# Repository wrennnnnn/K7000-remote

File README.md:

# K7000-remote
An OSH k7000 remote board.

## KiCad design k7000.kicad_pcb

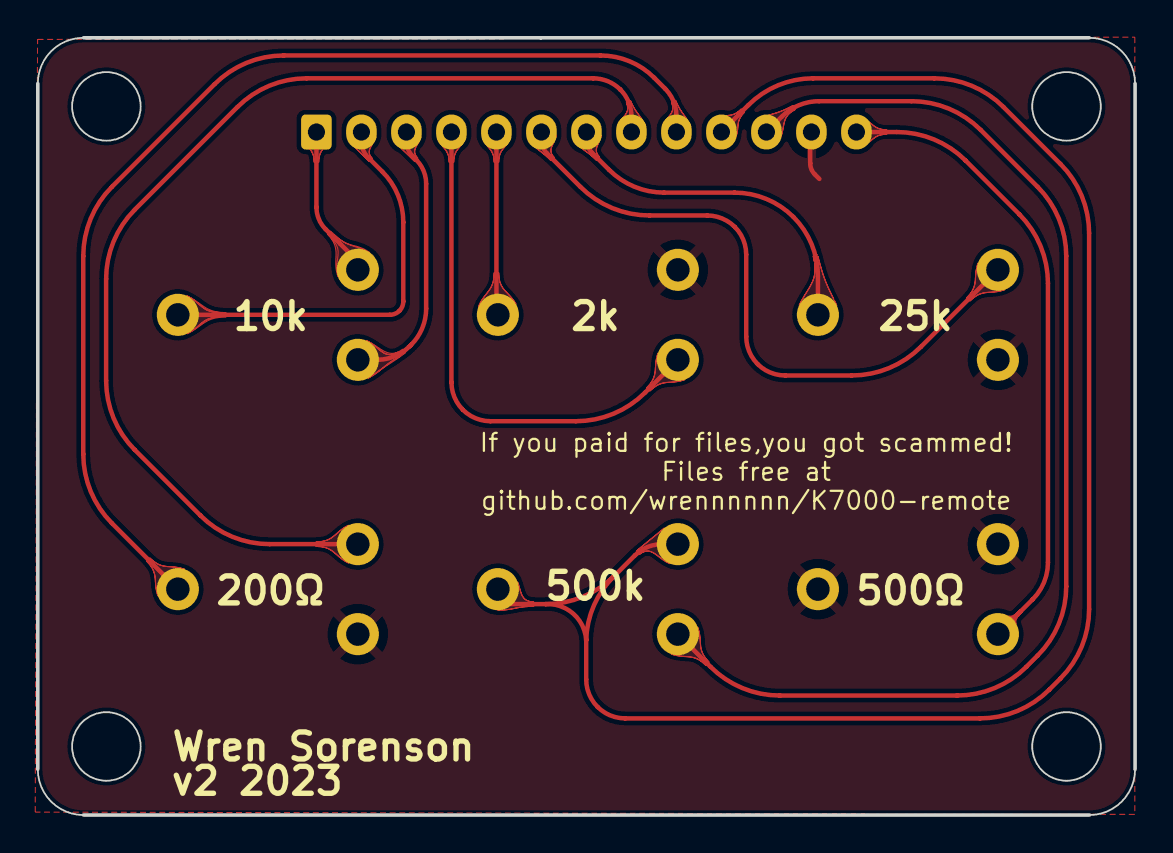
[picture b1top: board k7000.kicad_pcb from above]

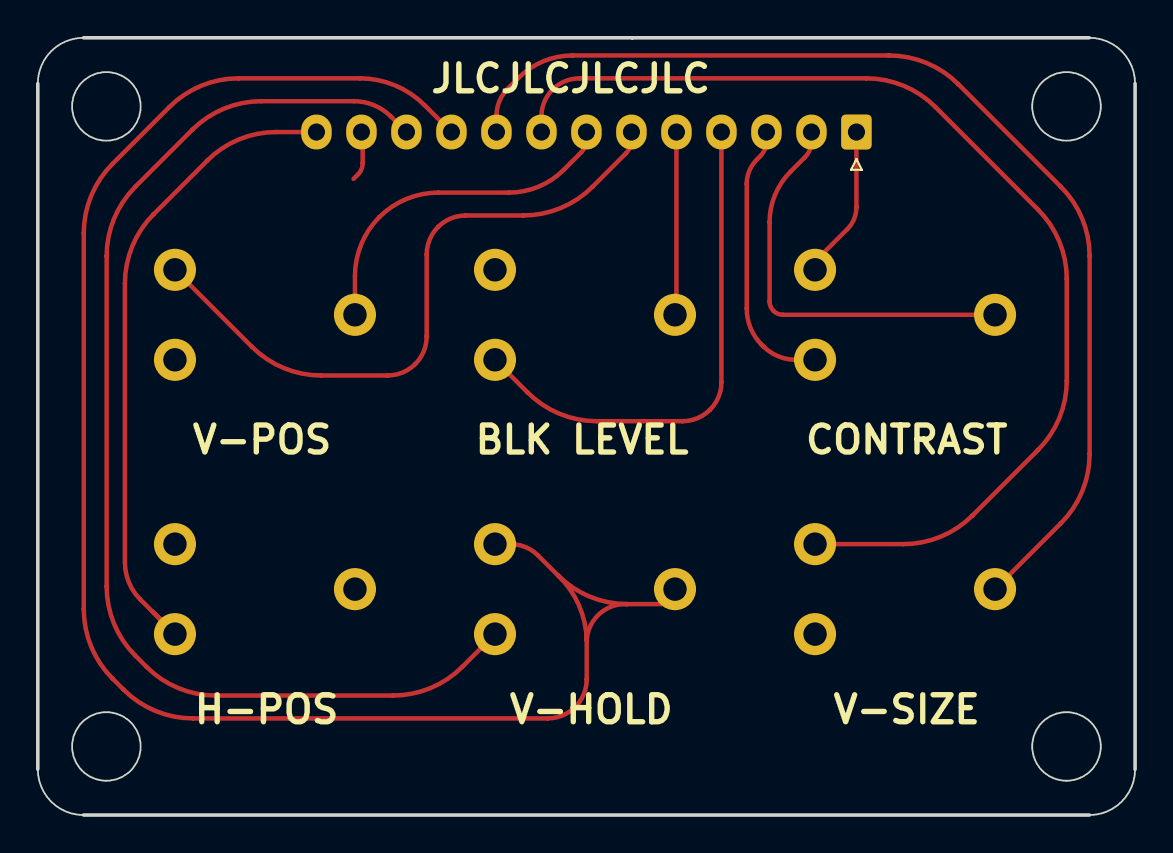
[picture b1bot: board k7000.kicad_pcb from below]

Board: 2 copper layers, 61.0 x 43.2 mm, 7 parts (7 on the bottom side), 13 nets.

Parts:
J1: Conn_01x13; JST_XH_S13B-XH-A-1_1x13_P2.50mm_Horizontal
RV1, RV2, RV3, RV4, RV5, RV6: R_Potentiometer_Trim; Potentiometer_Piher_PT-10-V10_Vertical

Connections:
unnamed: J1.3, RV1.1
unnamed: J1.2, RV1.2
unnamed: J1.1, RV1.3
unnamed: J1.12, RV2.1, RV3.3, RV5.1, RV6.2, RV6.3
unnamed: J1.9, RV2.2
unnamed: J1.8, RV2.3
unnamed: J1.4, RV3.1
unnamed: J1.5, RV3.2
unnamed: J1.11, RV4.1
unnamed: J1.10, RV4.2, RV4.3
unnamed: J1.7, RV5.2
unnamed: J1.6, RV5.3
unnamed: J1.13, RV6.1

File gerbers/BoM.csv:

"Id";"Designator";"Package";"Quantity";"Designation";"Supplier and ref";
1;"RV6,RV5,RV4,RV3,RV2,RV1";"Potentiometer_Piher_PT-10-V10_Vertical";6;"R_Potentiometer_Trim";;;
2;"J1";"JST_XH_S13B-XH-A-1_1x13_P2.50mm_Horizontal";1;"Conn_01x13";;;

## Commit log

2023-03-14 Main commit
    git is confusing :(
2023-03-14 fixed issues
    added silkscreen
2023-03-14 remade files
    added chamfer, flipped copper layer, added JLC watermark option for under the connector
2023-03-14 replaced gerbers
